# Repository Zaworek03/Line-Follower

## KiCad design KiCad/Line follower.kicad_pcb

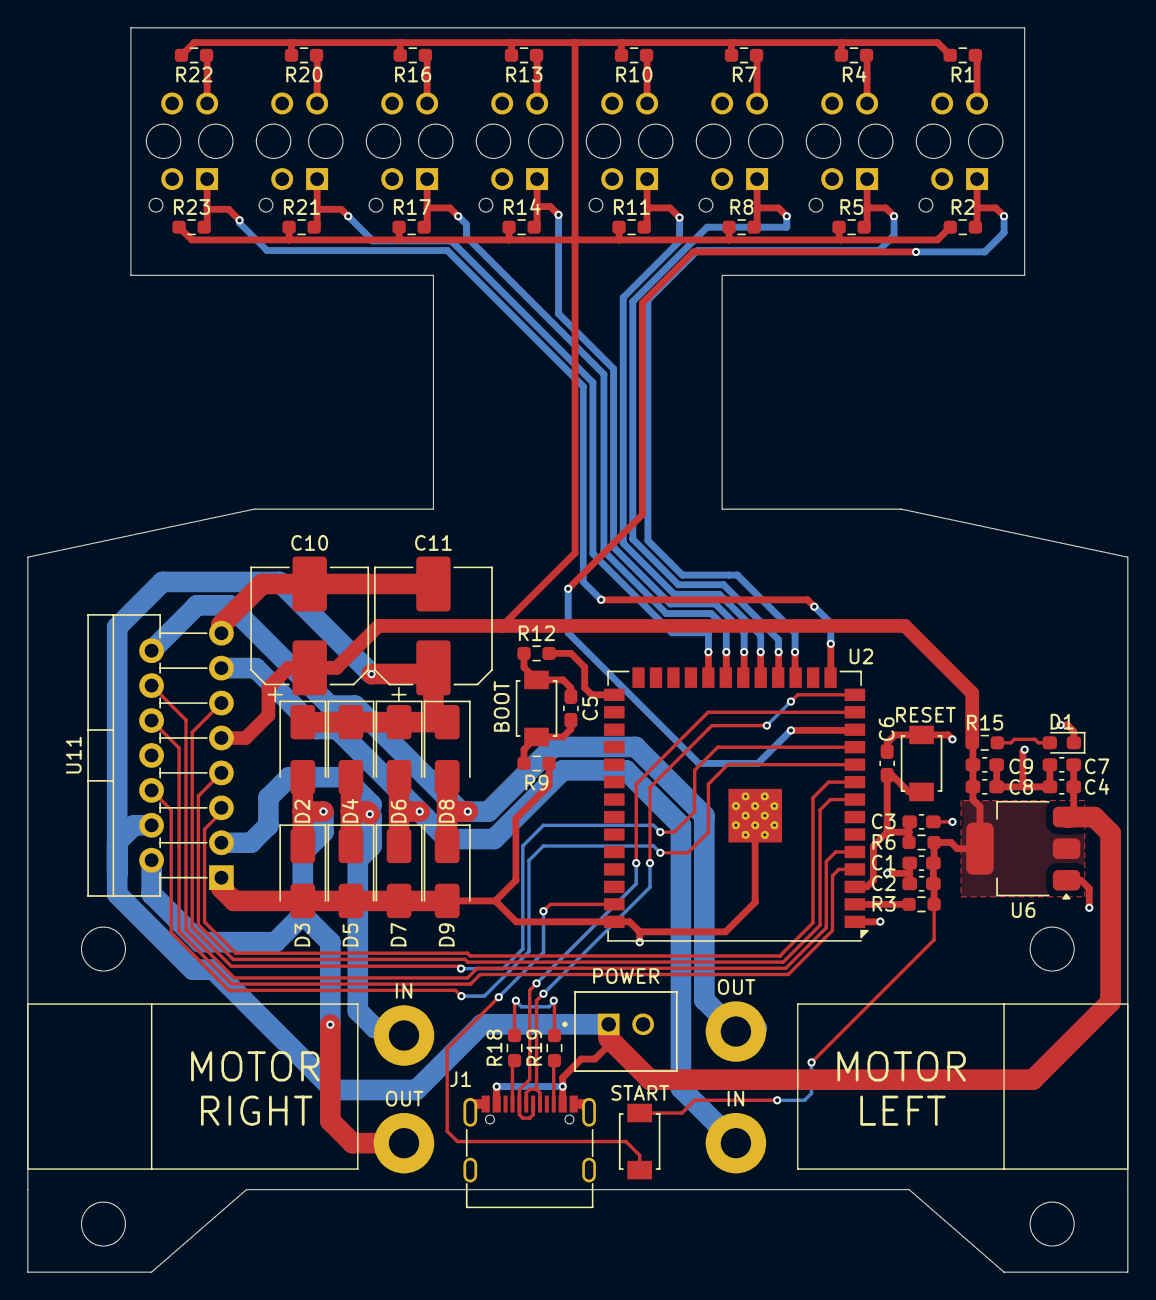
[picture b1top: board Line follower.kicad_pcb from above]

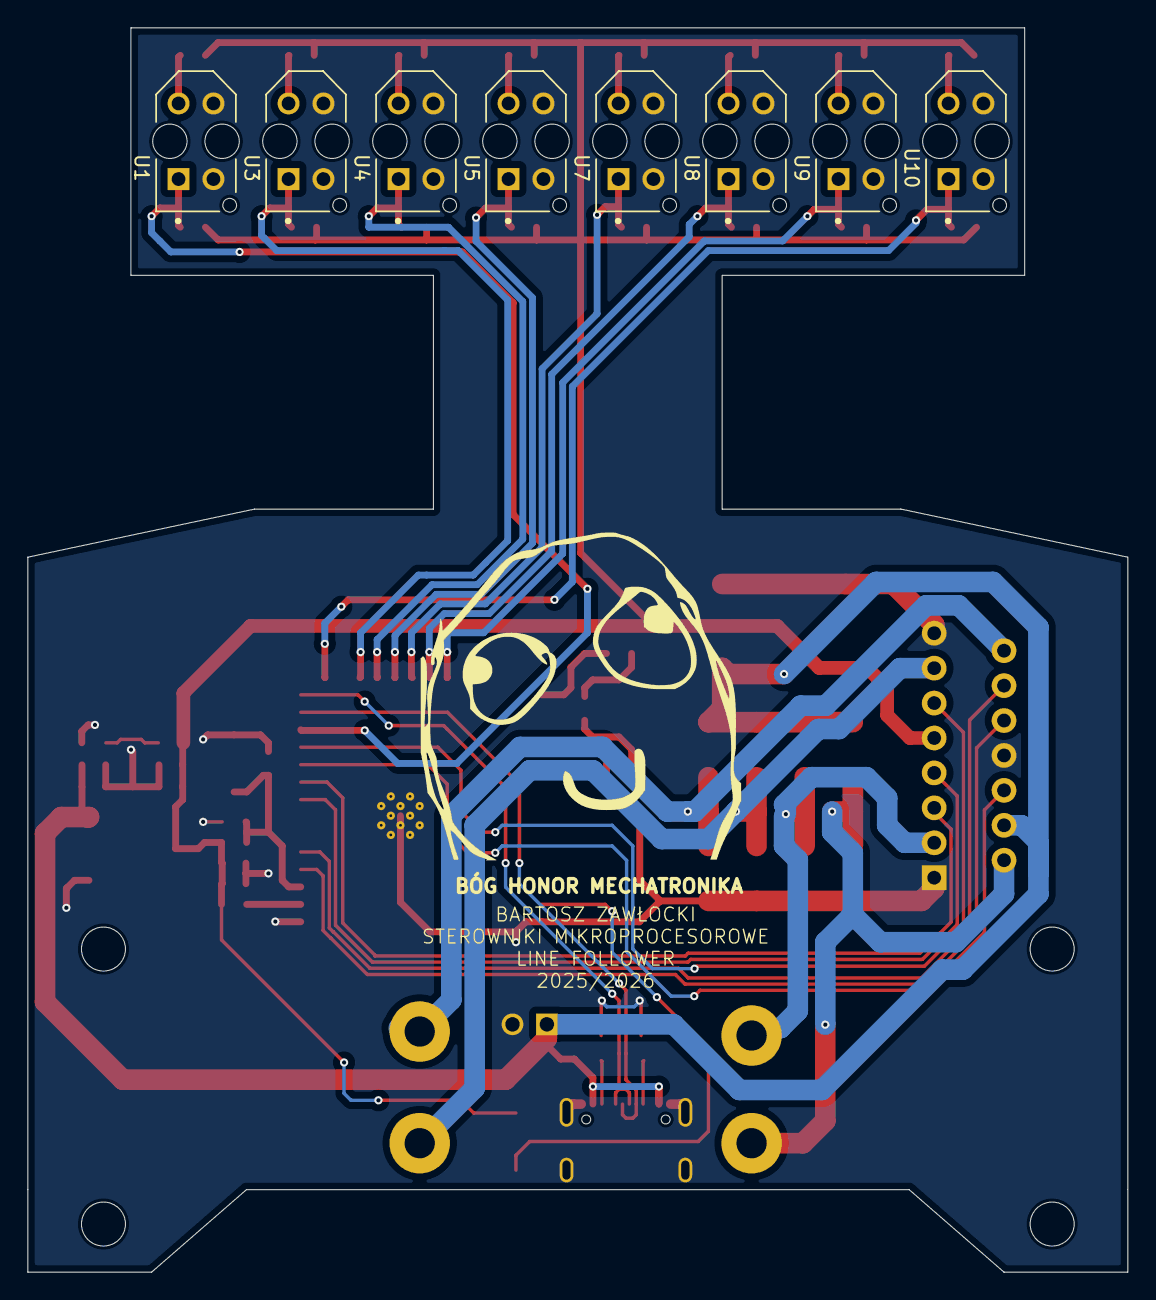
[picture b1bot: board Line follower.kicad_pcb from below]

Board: 2 copper layers, 80.0 x 90.5 mm, 67 parts (8 on the bottom side), 40 nets.

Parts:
BOOT: TS04-66-70-BK-260-SMT; SW_TS-1088-AR02016
C1, C4, C9: 10uF/25V(20%); C_0603_1608Metric_Pad1.08x0.95mm_HandSolder
C2, C6, C7, C8: 0.1uF/50V(10%); C_0603_1608Metric_Pad1.08x0.95mm_HandSolder
C3: 1uF/16V(10%); C_0603_1608Metric_Pad1.08x0.95mm_HandSolder
C5: 10nF; C_0603_1608Metric_Pad1.08x0.95mm_HandSolder
C10, C11: 220uF/35V; CP_Elec_8x6.2
D1: RED; LED_0603_1608Metric_Pad1.05x0.95mm_HandSolder
D2, D3, D4, D5, D6, D7, D8, D9: D; D_SMA
H1, H2, H3, H4: MountingHole; MountingHole_3.2mm_M3_DIN965
IN: MountingHole_Pad; MountingHole_2.2mm_M2_Pad
IN#2: MountingHole_Pad; MountingHole_2.2mm_M2_Pad
J1: USB_C_Receptacle_USB2.0_16P; USB_C_Receptacle_G-Switch_GT-USB-7010ASV
OUT: MountingHole_Pad; MountingHole_2.2mm_M2_Pad
OUT#2: MountingHole_Pad; MountingHole_2.2mm_M2_Pad
POWER: B2B-XH-A; JST_B2B-XH-A
R1, R4, R7, R10, R13, R16, R20, R22: 100R(1%); R_0603_1608Metric_Pad0.98x0.95mm_HandSolder
R2, R5, R8, R11, R14, R17, R21, R23: 5kR(1%); R_0603_1608Metric_Pad0.98x0.95mm_HandSolder
R3: 0R(1%); R_0603_1608Metric_Pad0.98x0.95mm_HandSolder
R6, R12: 10kR(1%); R_0603_1608Metric_Pad0.98x0.95mm_HandSolder
R9: 100kR(1%); R_0603_1608Metric_Pad0.98x0.95mm_HandSolder
R15: 1kR(1%); R_0603_1608Metric_Pad0.98x0.95mm_HandSolder
R18, R19: 5,1kR(1%); R_0603_1608Metric_Pad0.98x0.95mm_HandSolder
RESET: TS04-66-70-BK-260-SMT; SW_TS-1088-AR02016
START: TS04-66-70-BK-260-SMT; SW_TS-1088-AR02016
U1, U3, U4, U5, U7, U8, U9, U10: TCRT5000L; XDCR_TCRT5000L
U2: ESP32-S3-WROOM-1; ESP32-S3-WROOM-1U
U6: AMS1117-3.3; SOT-223-3_TabPin2
U11: L298N; TO-220-15_P2.54x5.08mm_StaggerOdd_Lead4.58mm_Vertical

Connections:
/AIN1: U2.9 (IO16), U11.5 (IN1)
/AIN2: U2.8 (IO15), U11.7 (IN2)
/BIN1: U2.4 (IO4), U11.10 (IN3)
/BIN2: U2.5 (IO5), U11.12 (IN4)
/CHIP_PU: C3.1, C6.1, R6.2, RESET.2, U2.3 (EN)
/ESP_3.3V: R3.1, U2.2 (3V3)
/EnA: U2.10 (IO17), U11.6 (EnA)
/EnB: U2.11 (IO18), U11.11 (EnB)
/GPIO0: R12.2, U2.27 (IO0)
/MOTORA IN: D8.2 (A), D9.1 (K), OUT.1, U11.14 (OUT4)
/MOTORA OUT: D6.2 (A), D7.1 (K), IN#2.1, U11.13 (OUT3)
/MOTORB IN: D4.2 (A), D5.1 (K), IN.1, U11.3 (OUT2)
/MOTORB OUT: D2.2 (A), D3.1 (K), OUT#2.1, U11.2 (OUT1)
/START: START.1, U2.39 (IO1)
/Sensor 1: R2.2, U1.1, U2.12 (IO8)
/Sensor 2: R5.2, U2.17 (IO9), U3.1
/Sensor 3: R8.2, U2.18 (IO10), U4.1
/Sensor 4: R11.2, U2.19 (IO11), U5.1
/Sensor 5: R14.2, U2.20 (IO12), U7.1
/Sensor 6: R17.2, U2.21 (IO13), U8.1
/Sensor 7: R21.2, U2.22 (IO14), U9.1
/Sensor 8: R23.2, U2.15 (IO3), U10.1
/USB_DN: J1.A7 (D-), J1.B7 (D-), U2.13 (USB_D-)
/USB_DP: J1.A6 (D+), J1.B6 (D+), U2.14 (USB_D+)
/VCC_3.3V: C1.1, C2.1, C8.1, C9.1, C10.1, R1.2, R2.1, R3.2, R4.2, R5.1, R6.1, R7.2, R8.1, R10.2, R11.1, R13.2, R14.1, R15.1, R16.2, R17.1, R20.2, R21.1, R22.2, R23.1, START.2, U6.2 (VO), U11.9 (Vss)
/VCC_5V: C4.1, C7.1, C11.1, D2.1 (K), D4.1 (K), D6.1 (K), D8.1 (K), J1.A4 (VBUS), J1.A9 (VBUS), J1.B4 (VBUS), J1.B9 (VBUS), POWER.1, U6.3 (VI), U11.4 (Vs)
GND: C1.2, C2.2, C3.2, C4.2, C6.2, C7.2, C8.2, C9.2, C10.2, C11.2, D1.1 (K), D3.2 (A), D5.2 (A), D7.2 (A), D9.2 (A), J1.A1 (GND), J1.A12 (GND), J1.B1 (GND), J1.B12 (GND), J1.S1 (SHIELD), POWER.2, R9.1, R18.2, R19.2, RESET.1, U1.2, U1.3, U2.1 (GND), U2.40 (GND), U2.41 (GND), U3.2, U3.3, U4.2, U4.3, U5.2, U5.3, U6.1 (GND), U7.2, U7.3, U8.2, U8.3, U9.2, U9.3, U10.2, U10.3, U11.1 (SENSE_A), U11.8 (GND), U11.15 (SENSE_B)
unnamed: BOOT.2, C5.1, R12.1
unnamed: BOOT.1, C5.2, R9.2
unnamed: D1.2 (A), R15.2
unnamed: J1.A5 (CC1), R18.1
unnamed: J1.B5 (CC2), R19.1
unnamed: R1.1, U1.4
unnamed: R4.1, U3.4
unnamed: R7.1, U4.4
unnamed: R10.1, U5.4
unnamed: R13.1, U7.4
unnamed: R16.1, U8.4
unnamed: R20.1, U9.4
unnamed: R22.1, U10.4

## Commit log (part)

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2025-11-26 Dodanie plików do projektu
    Dodałem wszystkie pliki z KiCad, Datasheet oraz dokumentacji technicznej
2025-11-26 Dodane not katalogowych
    Dodałem wszystkie noty katalogowe ważniejszych komponentów
